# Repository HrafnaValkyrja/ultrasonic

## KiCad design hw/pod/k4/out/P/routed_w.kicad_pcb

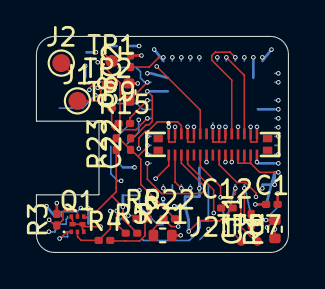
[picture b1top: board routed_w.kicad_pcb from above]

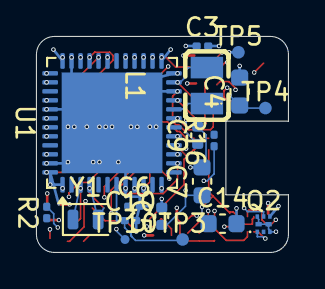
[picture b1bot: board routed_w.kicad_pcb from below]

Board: 6 copper layers, 14.0 x 12.0 mm, 42 parts (18 on the bottom side), 35 nets.

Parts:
C1, C2, C3, C6, C10, C11, C12, C22: C_0201_0603Metric
C4, C7, C14: C_0603_1608Metric
C5, C8, C9: C_0402_1005Metric
J1, J2: TestPoint_Pad_D1.0mm
J21: CONN-SMD_BM28B0.6-30DP-2-0.35V-51; BM28B0.6-30DP_2-0.35V
L1: L0806
Q1, Q2: Nexperia_SOT1216_DFN1010B-6
R1, R21: R_0402_1005Metric
R2, R3, R4, R5, R6, R15, R16, R22, R23: R_0201_0603Metric
TP1, TP2, TP3, TP4, TP5: TestPoint_Pad_D0.7mm
TP7, TP8, TP9, TP10: TestDot_D0.5mm
U1: QFN-48-1EP_7x7mm_P0.5mm_EP5.6x5.6mm
Y1: Crystal_SMD_2012-2Pin_2.0x1.2mm

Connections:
+3V0: C1.1, C2.1, C3.1, C4.1, C5.1, C6.1, C7.1, C14.1, J21.17, J21.18, J21.19, Q1.4, Q2.4, R3.2, R5.2, R15.2, R16.2, R23.1, TP4.1, U1.1, U1.9, U1.21, U1.25, U1.36, U1.48
BRIDGE_RTN: Q1.1, Q2.1, R21.1, R22.1
BTN: J21.29, U1.10
CHG_INT: J21.27, U1.38
DBG_TX: TP7.1, U1.42
GA_N: Q1.2, R4.1, U1.17
GA_P: Q1.5, R3.1, U1.29
GB_N: Q2.2, R6.1, U1.28
GB_P: Q2.5, R5.1, U1.31
GND: C1.2, C2.2, C3.2, C4.2, C5.2, C6.2, C7.2, C8.2, C9.2, C10.2, C11.2, C12.2, C14.2, C22.2, J21.1, J21.2, J21.4, J21.5, J21.8, J21.9, J21.10, J21.12, J21.14, J21.15, J21.16, J21.20, J21.21, J21.24, R1.2, R4.2, R6.2, R21.2, TP5.1, U1.8, U1.22, U1.24, U1.35, U1.41, U1.47, U1.49
I2C_SCL: J21.23, R15.1, U1.26
I2C_SDA: J21.25, R16.1, U1.27
I_SENSE: C22.1, R22.2, R23.2, U1.16
LED_K: J21.30, U1.43
LSE_IN: C11.1, U1.3, Y1.1
LSE_OUT: C12.1, U1.4, Y1.2
MDF_CCK: TP8.1, U1.45
MDF_SDI: TP9.1, U1.19
MIC_CLK: J21.3, R2.2
MIC_DATA: J21.7, TP10.1, U1.40
MIC_VDD: J21.6, U1.15
unnamed: R1.1, U1.44
unnamed: R2.1, U1.39
NRST: C10.1, TP3.1, U1.7
OUT_A: J1.1, Q1.3, Q1.6, Q1.7, Q1.8
OUT_B: J2.1, Q2.3, Q2.6, Q2.7, Q2.8
SWCLK: TP2.1, U1.37
SWDIO: TP1.1, U1.34
TS: J21.22, U1.12
USB_DM: J21.13, U1.32
USB_DP: J21.11, U1.33
VBAT_SENSE: J21.28, U1.14
VBUS_SENSE: J21.26, U1.11
VDD11: C8.1, C9.1, L1.2, U1.23, U1.46
VLXSMPS: L1.1, U1.20

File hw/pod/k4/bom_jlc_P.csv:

Comment,Designator,Footprint,LCSC Part #,Qty,In sourcing lock
100n,"C1,C10,C2,C3,C6",C_0201_0603Metric,C76934,5,yes
8p2,"C11,C12",C_0201_0603Metric,C161441,2,yes
22u,C14,C_0603_1608Metric,C59461,1,yes
10n,C22,C_0201_0603Metric,C85930,1,yes
10u,"C4,C7",C_0603_1608Metric,C19702,2,yes
1u,C5,C_0402_1005Metric,C52923,1,yes
2u2 10V,"C8,C9",C_0402_1005Metric,C107369,2,yes
BM28B0.6-30DP/2-0.35V(51),J21,BM28B0.6-30DP_2-0.35V,C424570,1,dated lookup
2u2,L1,L0806,C337891,1,yes
PMCXB290UE,"Q1,Q2",Nexperia_SOT1216_DFN1010B-6,C19654206,2,yes
10k,R1,R_0402_1005Metric,C25744,1,yes
10k,"R15,R16",R_0201_0603Metric,C473048,2,yes
33,R2,R_0201_0603Metric,C473457,1,yes
0.1,R21,R_0402_1005Metric,C409058,1,yes
1k,R22,R_0201_0603Metric,C270365,1,yes
1M,R23,R_0201_0603Metric,C473482,1,yes
100k,"R3,R4,R5,R6",R_0201_0603Metric,C270364,4,yes
STM32U575CIUxQ,U1,QFN-48-1EP_7x7mm_P0.5mm_EP5.6x5.6mm,C5271013,1,yes
32.768k 7pF,Y1,Crystal_SMD_2012-2Pin_2.0x1.2mm,C99009,1,yes

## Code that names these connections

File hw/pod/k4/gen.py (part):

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them to the rails with C14 behind. 14 -> 11 Extended part types.
Rev F (2026-10-02, Phase 1 "logical simplification" from docs/research/simplification-study.md, package B3 =
B on the owner-decision defaults; owner phases: Phase 1 logic, then her board review, then Phase 2 miniaturization):
- removed R11 (ROM loader pulls PA10 up itself, AN2606 Table 199; PA10 then reused as GB_P, ECR-0003), R17 (CHG_INT uses the PA15 internal
  pull-up; PB5 strapped to GND so the UCPD dead-battery 5.1k pull-down can't arm on PA15, ECR-0013 S1), R19 (CC
  sense; PA3 spare; ILIM policy by enumeration, Rd R18 + J12 stay), C20 (VBAT pin 1 shares the pin-48 100 nF placed
  <= 1.5 mm from both, PER-06), D1/D2 (DNP footprints, OUT-04).
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- J4 (dock GND) and J6 (cell -) merged into one 1.0 x 2.0 mm GND pad J4, placed between J3 DOCK_VBUS and J5 VBAT
  (ASM-09: a solder bridge can no longer put the cell on an exposed contact).
- C15 (charger IN) 4.7 uF 10 V -> 25 V (TI SLUSE99C 9.2.2.1 recommends 25 V-rated caps on IN; ECR-0013 S3).
- debug/fallback dots (PER-12, O18): TP7 PB6 USART1_TX printf; TP8 PB8 MDF1_CCK0 + TP9 PB1 MDF1_SDI0 + TP10 MIC_DATA
  = hand-wire recovery to the MDF if the ADF mic-clock duty is bad (sub-audio-in issue 5).
- Q1/Q2 on the Nexperia Fig. 32 land pattern (ECR-0004, hw/lib/pod.pretty, docs/research/sot1216-footprint.md).
- bridge leg B moved from TIM1_CH2/CH2N (PA9/PB0) to TIM1_CH3/CH3N (PA10/PB15, AF1; ECR-0003): frees the jammed
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              footprint="lcsc:Knowles_LGA-5_3.5x2.65mm_Port0.6")   # 0.6 mm port (stock is 0.5)
    u2.fields["LCSC"] = "C2879853"
    mic_vdd, mic_clk, mic_dat = Net("MIC_VDD"), Net("MIC_CLK"), Net("MIC_DATA")
    mic_vdd.drive = skidl.POWER                        # a GPIO is the supply here, on purpose
    mic_vddf = Net("MIC_VDDF")                         # K4 (2026-10-08): local RC filter at the mic; MIC_VDD (PA5 + BM28 pin 6) is the unfiltered side
    mic_vdd += u1["PA5"]                               # ~1 mA from a GPIO; off in Off mode (D12)
    r = R("R30", "33", "R33"); r[1] += mic_vdd; r[2] += mic_vddf       # 33R x 1.35 mA (params.yaml mic.r_load 2.2k @3 V) = 45 mV < 50 mV; corner 1/(2pi 33R ~70nF derated C13) = ~69 kHz, 3 MHz is 33 dB down
    mic_vddf += u2["VDD"]
    c = C("C13", "100n", "C100n"); c[1] += mic_vddf; c[2] += gnd       # X7R: no 0402 C0G at 100 nF
    r = R("R2", "33", "R33"); r[1] += u1["PB3"]; r[2] += mic_clk       # tames the 4 MHz clock edge
    mic_clk += u2["CLOCK"]
    mic_dat += u2["DATA"], u1["PB4"]
    gnd += u2["GND"], u2["SEL"]                        # SELECT tied (D13)
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    u3.fields["LCSC"] = "C3682423"
    u3["IN"] += vbus; u3["SYS"] += vsys; u3["BAT"] += vbat; u3["GND"] += gnd
    scl, sda, chg_int, ts = Net("I2C_SCL"), Net("I2C_SDA"), Net("CHG_INT"), Net("TS")
    scl += u3["SCL"], u1["PB13"]; sda += u3["SDA"], u1["PB14"]; chg_int += u3["/INT"], u1["PA15"]
    for rref, n in (("R15", scl), ("R16", sda)):                        # Rev F: CHG_INT uses the PA15 internal pull-up (R17 gone)
        r = R(rref, "10k", "R10k"); r[1] += n; r[2] += v3
    gnd += u1["PB5"]                                                     # strap: a high on PB5 would arm the UCPD 5.1k pull-down on PA15 (ECR-0013 S1)
    ts += u3["TS/MR"], u1["PA2"]                                         # firmware reads TS for the 20 C rule
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    c = C("C17", "1u 16V", "C1u_16V_0201", C0201); c[1] += vsys; c[2] += gnd
    c = C("C18", "1u", "C1u"); c[1] += v3_ldo; c[2] += gnd           # stays at the LDO for stability
    r = R("R20", "0", "R0"); r[1] += v3_ldo; r[2] += v3                # lift: measure or inject the 3V0 rail
    vs = Net("VBAT_SENSE")                                              # 1M/1M: 2 uA, 2.1 V max at PA4
    r = R("R8", "1M", "R1M"); r[1] += vbat; r[2] += vs
    r = R("R9", "1M", "R1M"); r[1] += vs; r[2] += gnd
    c = C("C19", "100n", "C100n"); c[1] += vs; c[2] += gnd              # holds the node for the ADC sample
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    sw = Part("lcsc", "KMT022NGJLHS", ref="SW1", tag="SW1", footprint="lcsc:SW-SMD_4P-L3.0-W2.6-P1.85-LS3.4")
    sw.fields["LCSC"] = "C221707"
    btn = Net("BTN")
    v3 += sw[1], sw[2]; btn += sw[3], sw[4]; btn += u1["PA0"]          # WKUP1, active high
    r = R("R10", "2k2", "R2k2"); r[1] += btn; r[2] += gnd             # >= 1 mA through the contact when pressed
    # power-indicator LED, off-board in the pad housing (docs/research/pad-led.md). Fed from VSYS (R14):
    # a blue LED needs ~2.7 V, too close to the 3.0 V rail. PB7 is 5 V tolerant (FT, DS13737 Rev 8).
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    r = R("R14", "2k2", "R2k2"); r[1] += vsys; r[2] += led_a
    p = pad("J7", "LED+"); p[1] += led_a
    p = pad("J8", "LED-"); p[1] += led_k
    led_k += u1["PB7"]
    for ref, lab, n in (("TP1", "SWDIO", Net("SWDIO")), ("TP2", "SWCLK", Net("SWCLK")),
                        ("TP3", "NRST", nrst), ("TP4", "3V0", v3), ("TP5", "GND", gnd),
                        ("TP6", "VSYS", vsys)):
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            n += u1["PA14"]
    # Rev F debug / fallback dots (PER-12, O18): printf on USART1_TX, and a hand-wire path to the MDF if the ADF
    # mic-clock duty is out of spec (lift R2, wire TP8 to R2's mic-side pad, TP9 to TP10; firmware moves to MDF1)
    for ref, lab, n, pin in (("TP7", "DBG_TX", Net("DBG_TX"), "PB6"), ("TP8", "MDF_CCK", Net("MDF_CCK"), "PB8"),
                             ("TP9", "MDF_SDI", Net("MDF_SDI"), "PB1")):
        p = pad(ref, lab, PAD_DOT); p[1] += n; n += u1[pin]
    p = pad("TP10", "MIC_DATA", PAD_DOT); p[1] += mic_dat
    # spare pins, left free on purpose; PC13 stays static next to the crystal (ES0499 2.2.1); PB15 carries the UCPD
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    "R12", "R13", "R8", "R9", "C19",               # VBUS / VBAT sense dividers (analogue nodes cross as VBUS_SENSE / VBAT_SENSE)
    "RT1", "J9", "J5",                             # NTC, NTC pad, cell BAT+ wire pad (cell - lands on dock GND pad J4, ASM-09)
    "SW1", "R10",                                  # button (+3V0 from the LDO on M; BTN crosses)
    "R14", "J7", "J8",                             # LED feed (VSYS), LED wire pads; LED_K crosses to PB7
    "TP4", "TP5", "TP10", "R15", "R16")}           # 2026-10-08 unload P->M (ECR-0020 rev 4): +3V0/GND/MIC_DATA pads, I2C pull-ups (+3V0 is on M)
# Everything not listed is P.
BM28_PINS = {    # pin -> net. Footprint numbering: pads 1-15 one row, 16-30 the other; pad n faces pad 31-n; the 180-deg reversed mate pairs n <-> n+/-15 [V: footprint geometry].
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    11: "USB_DM", 12: "GND", 13: "USB_DP", 14: "GND", 15: "+3V0", 16: "GND", 17: "GND", 18: "GND", 19: "LED_K", 20: "GND",
    21: "MIC_DATA", 22: "GND", 23: "CHG_INT", 24: "GND", 25: "BTN", 26: "GND", 27: "VBUS_SENSE", 28: "GND",
    29: "TS", 30: "+3V0", 31: "+3V0", 32: "+3V0", 33: "+3V0", 34: "+3V0"}
    # (assignment follows U1's pin geography: west MIC_VDD/VBAT, north SCL/SDA/USB, south BTN/VBUS/TS, east LED_K/MIC_DATA/CHG_INT; signals on N-row odd pads 1-13 and S-row odd pads 19-29)
# Current budget [V sim/checks/k4_checks: bridge peak 315 mA, mean < 0.1 A, charger/VSYS never crosses]: +3V0 on 2 signal contacts + 2 power contacts (5 A):
# worst contact 0.16 A at signal contacts if the tabs carried nothing, vs 0.3 A rating; GND return over 15 pins + shield. USB D+/D- and the MIC trio are GND-shielded both sides.
# Reversal (n <-> n+/-15): signal-GND x13, +3V0-+3V0 x2 (+4 tabs pairwise), GND-GND x15: no short, nothing driven into a GPIO.
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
